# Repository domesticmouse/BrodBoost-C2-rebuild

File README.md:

# BrødBoost C2 Rebuild

This is a rebuild of Axiometa's [BrodBoost C2](https://github.com/axiometa/BrodBoost-C2).

This is purely for learning purposes.

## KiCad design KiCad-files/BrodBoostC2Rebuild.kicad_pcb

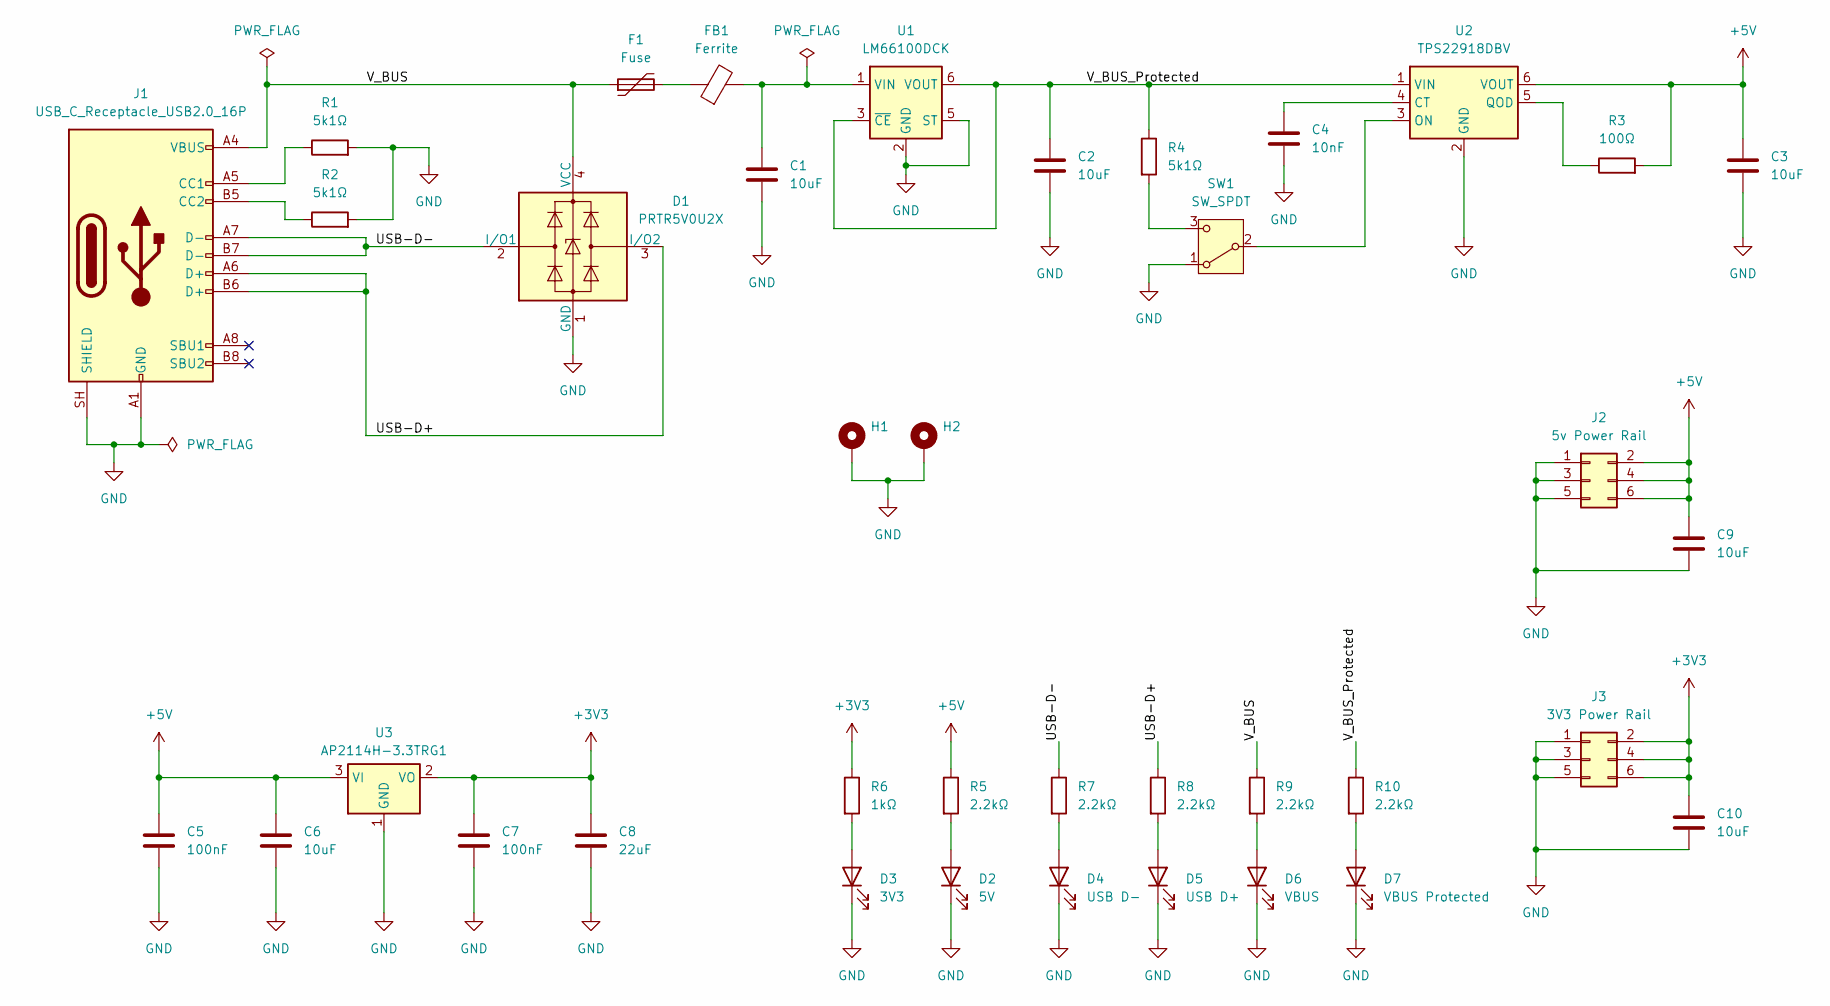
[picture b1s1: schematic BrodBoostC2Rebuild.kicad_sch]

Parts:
C1, C2, C3, C6, C9, C10: 10uF; C_0805_2012Metric_Pad1.18x1.45mm_HandSolder
C4: 10nF; C_0805_2012Metric_Pad1.18x1.45mm_HandSolder
C5, C7: 100nF; C_0805_2012Metric_Pad1.18x1.45mm_HandSolder
C8: 22uF; C_0805_2012Metric_Pad1.18x1.45mm_HandSolder
D1: PRTR5V0U2X; SOT-143; LCSC C5158049
D2: 5V; LED_0805_2012Metric_Pad1.15x1.40mm_HandSolder; LCSC C84256
D3: 3V3; LED_0805_2012Metric_Pad1.15x1.40mm_HandSolder; LCSC C84256
D4: USB D-; LED_0805_2012Metric_Pad1.15x1.40mm_HandSolder; LCSC C84256
D5: USB D+; LED_0805_2012Metric_Pad1.15x1.40mm_HandSolder; LCSC C84256
D6: VBUS; LED_0805_2012Metric_Pad1.15x1.40mm_HandSolder; LCSC C84256
D7: VBUS Protected; LED_0805_2012Metric_Pad1.15x1.40mm_HandSolder; LCSC C84256
F1: Fuse; Fuse_0805_2012Metric_Pad1.15x1.40mm_HandSolder; LCSC C22363531
FB1: Ferrite; FerriteBead_0805_2012Metric_Pad1.20x1.40mm_HandSolder; LCSC C76818
H1, H2: MountingHole_Pad; MountingHole_3.2mm_M3_Pad
J1: USB_C_Receptacle_USB2.0_16P; USB_C_Receptacle_XKB_U262-16XN-4BVC11; LCSC C2927038
J2: 5v Power Rail; PinHeader_2x03_P2.54mm_Vertical
J3: 3V3 Power Rail; PinHeader_2x03_P2.54mm_Vertical
R1, R2, R4: 5k1Ω; R_0805_2012Metric_Pad1.20x1.40mm_HandSolder
R3: 100Ω; R_0805_2012Metric_Pad1.20x1.40mm_HandSolder
R5, R7, R8, R9, R10: 2.2kΩ; R_0805_2012Metric_Pad1.20x1.40mm_HandSolder
R6: 1kΩ; R_0805_2012Metric_Pad1.20x1.40mm_HandSolder
SW1: SW_SPDT; SW_Slide_SPDT_Straight_CK_OS102011MS2Q; LCSC C2939725
U1: LM66100DCK; SOT-363_SC-70-6; LCSC C2869734
U2: TPS22918DBV; SOT-23-6; LCSC C131941
U3: AP2114H-3.3TRG1; SOT-223-3_TabPin2; LCSC C150716

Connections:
+3V3: C7.1, C8.1, C10.1, J3.2, J3.4, J3.6, R6.1, U3.2 (VO)
+5V: C3.1, C5.1, C6.1, C9.2, J2.2, J2.4, J2.6, R3.2, R5.1, U2.6 (VOUT), U3.3 (VI)
/USB-D+: D1.3 (I/O2), J1.A6 (D+), J1.B6 (D+), R8.1
/USB-D-: D1.2 (I/O1), J1.A7 (D-), J1.B7 (D-), R7.1
/V_BUS: D1.4 (VCC), F1.1, J1.A4 (VBUS), J1.A9 (VBUS), J1.B4 (VBUS), J1.B9 (VBUS), R9.1
/V_BUS_Protected: C2.1, R4.1, R10.1, U1.3 (~CE), U1.6 (VOUT), U2.1 (VIN)
GND: C1.2, C2.2, C3.2, C4.2, C5.2, C6.2, C7.2, C8.2, C9.1, C10.2, D1.1 (GND), D2.1 (K), D3.1 (K), D4.1 (K), D5.1 (K), D6.1 (K), D7.1 (K), H1.1 (1_1), H2.1 (1_1), J1.A1 (GND), J1.A12 (GND), J1.B1 (GND), J1.B12 (GND), J1.SH (SHIELD), J2.1, J2.3, J2.5, J3.1, J3.3, J3.5, R1.2, R2.2, SW1.1 (A), U1.2 (GND), U1.5 (ST), U2.2 (GND), U3.1 (GND)
unnamed: D2.2 (A), R5.2
unnamed: D3.2 (A), R6.2
unnamed: D4.2 (A), R7.2
unnamed: D5.2 (A), R8.2
unnamed: D6.2 (A), R9.2
unnamed: D7.2 (A), R10.2
unnamed: F1.2, FB1.1
unnamed: J1.A5 (CC1), R1.1
unnamed: J1.B5 (CC2), R2.1
unnamed: SW1.2 (B), U2.3 (ON)
unnamed: R4.2, SW1.3 (C)
unnamed: C1.1, FB1.2, U1.1 (VIN)
unnamed: C4.1, U2.4 (CT)
unnamed: R3.1, U2.5 (QOD)

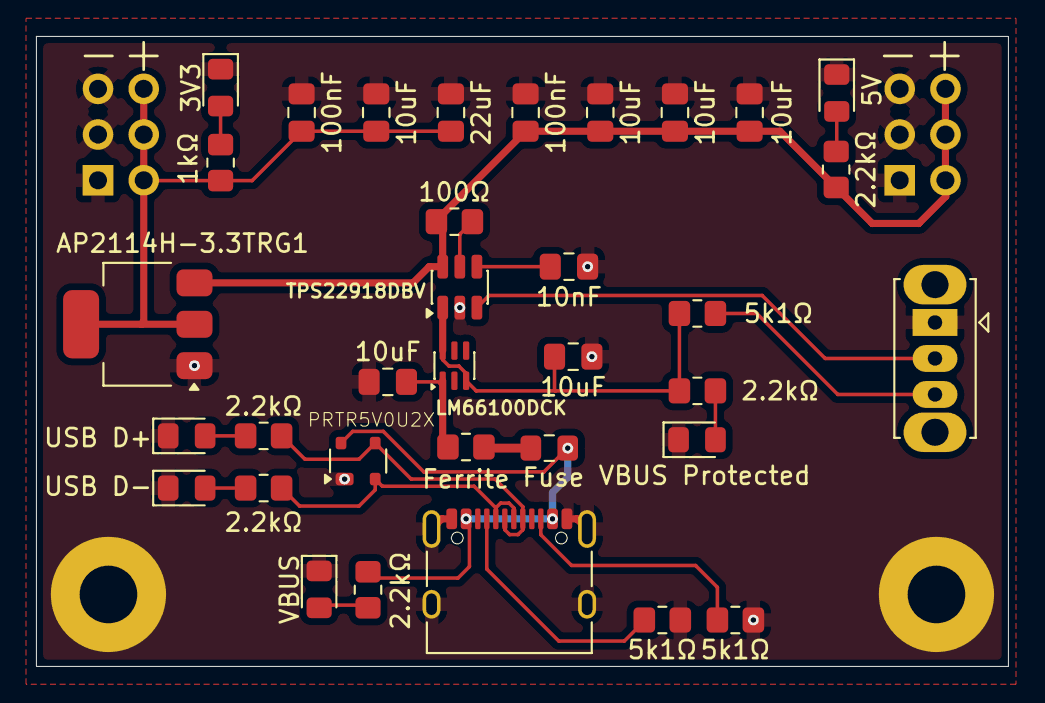
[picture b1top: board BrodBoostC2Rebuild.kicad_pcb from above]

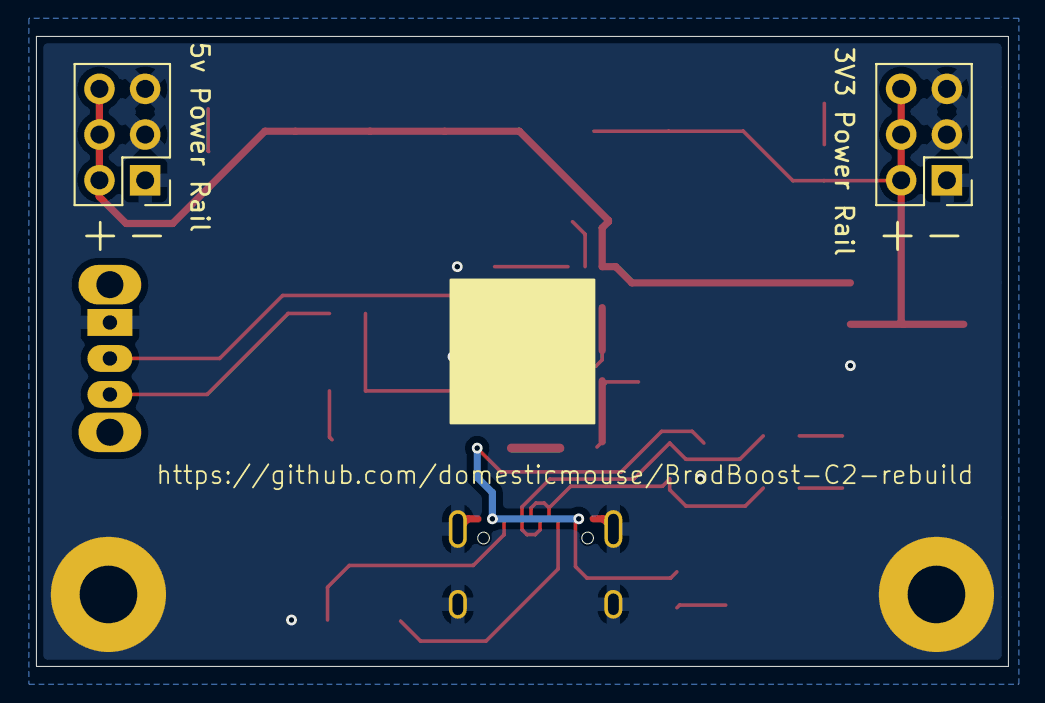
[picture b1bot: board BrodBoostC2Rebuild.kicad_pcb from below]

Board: 2 copper layers, 54.0 x 35.0 mm, 38 parts (2 on the bottom side), 21 nets.

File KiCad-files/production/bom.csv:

Designator,Footprint,Quantity,Value,LCSC Part #
"C1, C10, C2, C3, C6, C9",0805,6,10uF,
C4,0805,1,10nF,
"C5, C7",0805,2,100nF,
C8,0805,1,22uF,
D1,SOT-143,1,PRTR5V0U2X,C5158049
D2,0805,1,5V,C84256
D3,0805,1,3V3,C84256
D4,0805,1,USB D-,C84256
D5,0805,1,USB D+,C84256
D6,0805,1,VBUS,C84256
D7,0805,1,VBUS Protected,C84256
F1,0805,1,Fuse,C22363531
FB1,FerriteBead_0805_2012Metric_Pad1.20x1.40mm_HandSolder,1,Ferrite,C76818
J1,USB_C_Receptacle_XKB_U262-16XN-4BVC11,1,USB_C_Receptacle_USB2.0_16P,C2927038
J2,PinHeader_2x03_P2.54mm_Vertical,1,5v Power Rail,
J3,PinHeader_2x03_P2.54mm_Vertical,1,3V3 Power Rail,
"R1, R2, R4",0805,3,5k1Ω,
"R10, R5, R7, R8, R9",0805,5,2.2kΩ,
R3,0805,1,100Ω,
R6,0805,1,1kΩ,
SW1,SW_Slide_SPDT_Straight_CK_OS102011MS2Q,1,SW_SPDT,C2939725
U1,SOT-363_SC-70-6,1,LM66100DCK,C2869734
U2,SOT-23-6,1,TPS22918DBV,C131941
U3,SOT-223-3_TabPin2,1,AP2114H-3.3TRG1,C150716

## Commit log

2026-04-22 Added schematic
2026-04-23 Add PCB
2026-04-23 Update parts
2026-04-25 Updated board
2026-05-07 Updated schematic
